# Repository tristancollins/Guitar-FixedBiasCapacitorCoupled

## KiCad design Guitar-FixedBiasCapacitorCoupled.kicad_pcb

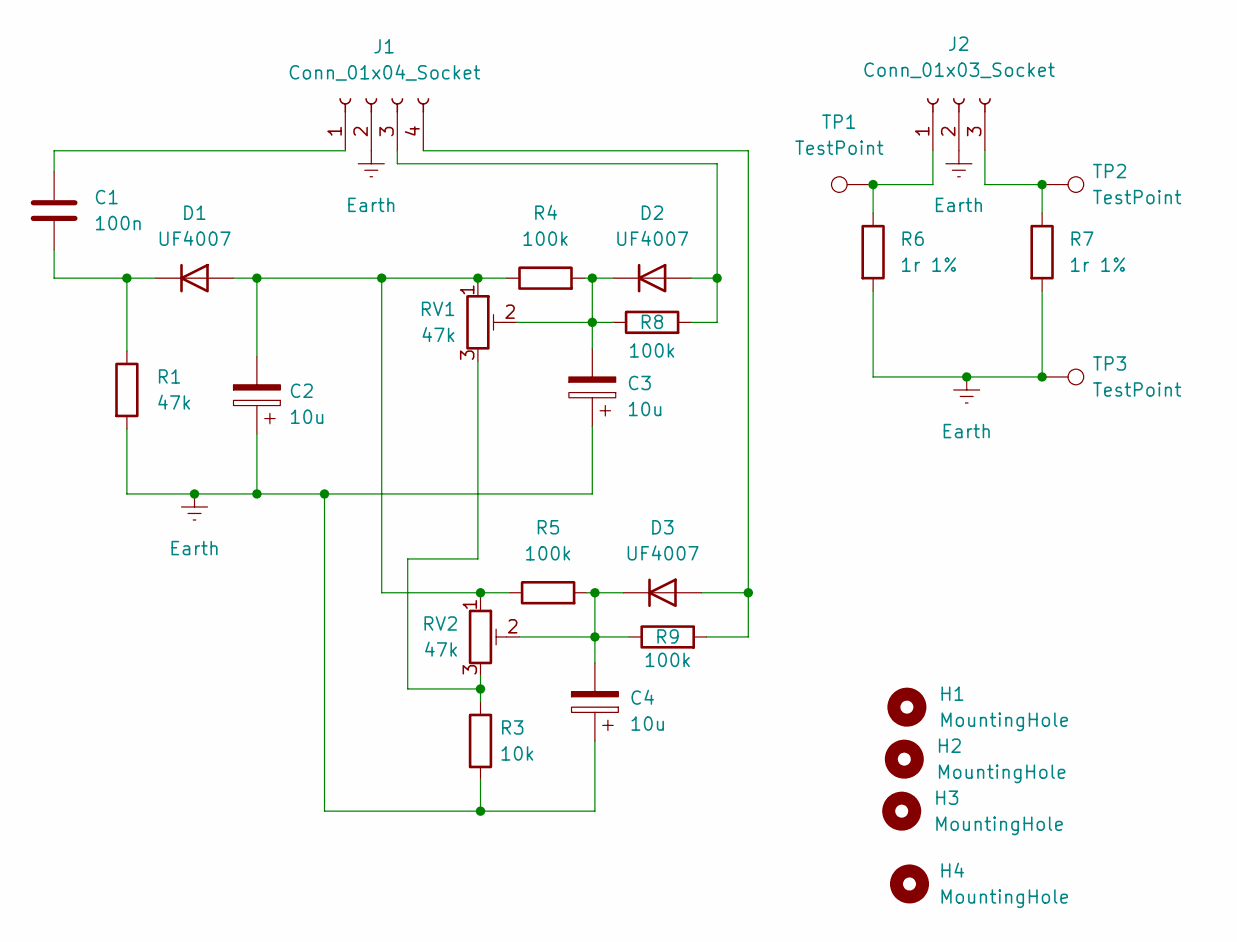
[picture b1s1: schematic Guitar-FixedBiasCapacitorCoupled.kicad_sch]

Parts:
C1: 100n; C_Axial_L17.0mm_D7.0mm_P25.00mm_Horizontal
C2, C3, C4: 10u; CP_Radial_D5.0mm_P2.50mm
D1, D2, D3: UF4007; D_DO-35_SOD27_P3.81mm_Vertical_AnodeUp
H1, H2, H3, H4: MountingHole; MountingHole_3.2mm_M3
J1: Conn_01x04_Socket; PinSocket_1x04_P2.54mm_Vertical
J2: Conn_01x03_Socket; PinSocket_1x03_P2.54mm_Vertical
R1: 47k; R_Axial_DIN0309_L9.0mm_D3.2mm_P2.54mm_Vertical
R3: 10k; R_Axial_DIN0309_L9.0mm_D3.2mm_P2.54mm_Vertical
R4, R5, R8, R9: 100k; R_Axial_DIN0309_L9.0mm_D3.2mm_P2.54mm_Vertical
R6, R7: 1r 1%; R_Axial_DIN0309_L9.0mm_D3.2mm_P2.54mm_Vertical
RV1, RV2: 47k; Potentiometer_Bourns_3339P_Vertical
TP1, TP2, TP3: TestPoint; TestPoint_Keystone_5005-5009_Compact

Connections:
Earth: C2.1, C3.1, C4.1, J1.2, J2.2, R1.2, R3.2, R6.2, R7.2, TP3.1
unnamed: C2.2, D1.2 (A), R4.1, R5.1, RV1.1, RV2.1
unnamed: C1.2, D1.1 (K), R1.1
unnamed: D2.2 (A), J1.3, R8.2
unnamed: C3.2, D2.1 (K), R4.2, R8.1, RV1.2
unnamed: D3.2 (A), J1.4, R9.2
unnamed: C4.2, D3.1 (K), R5.2, R9.1, RV2.2
unnamed: C1.1, J1.1
unnamed: J2.1, R6.1, TP1.1
unnamed: J2.3, R7.1, TP2.1
unnamed: R3.1, RV1.3, RV2.3

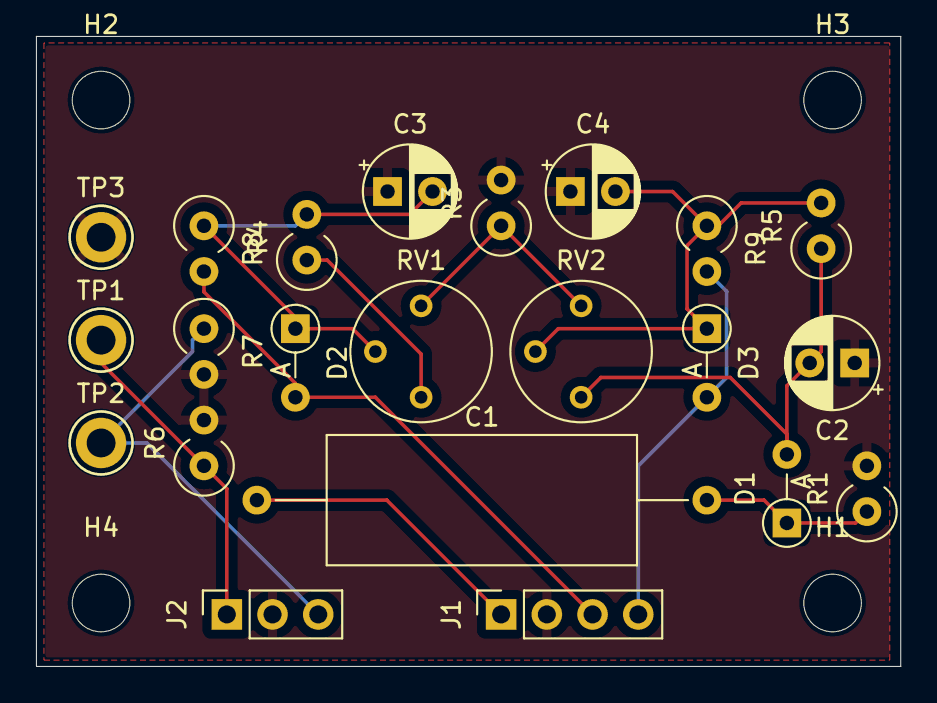
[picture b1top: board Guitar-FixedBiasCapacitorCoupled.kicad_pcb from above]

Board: 2 copper layers, 48.0 x 35.0 mm, 26 parts (0 on the bottom side), 11 nets.
